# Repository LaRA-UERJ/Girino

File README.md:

# Girino
Plataforma didática do LaRA para ensino de controle de motores DC. Integra microcontrolador, driver MOSFET e encoder em uma bancada compacta para introdução prática à leitura de sensores, modulação PWM e controle em malha fechada.

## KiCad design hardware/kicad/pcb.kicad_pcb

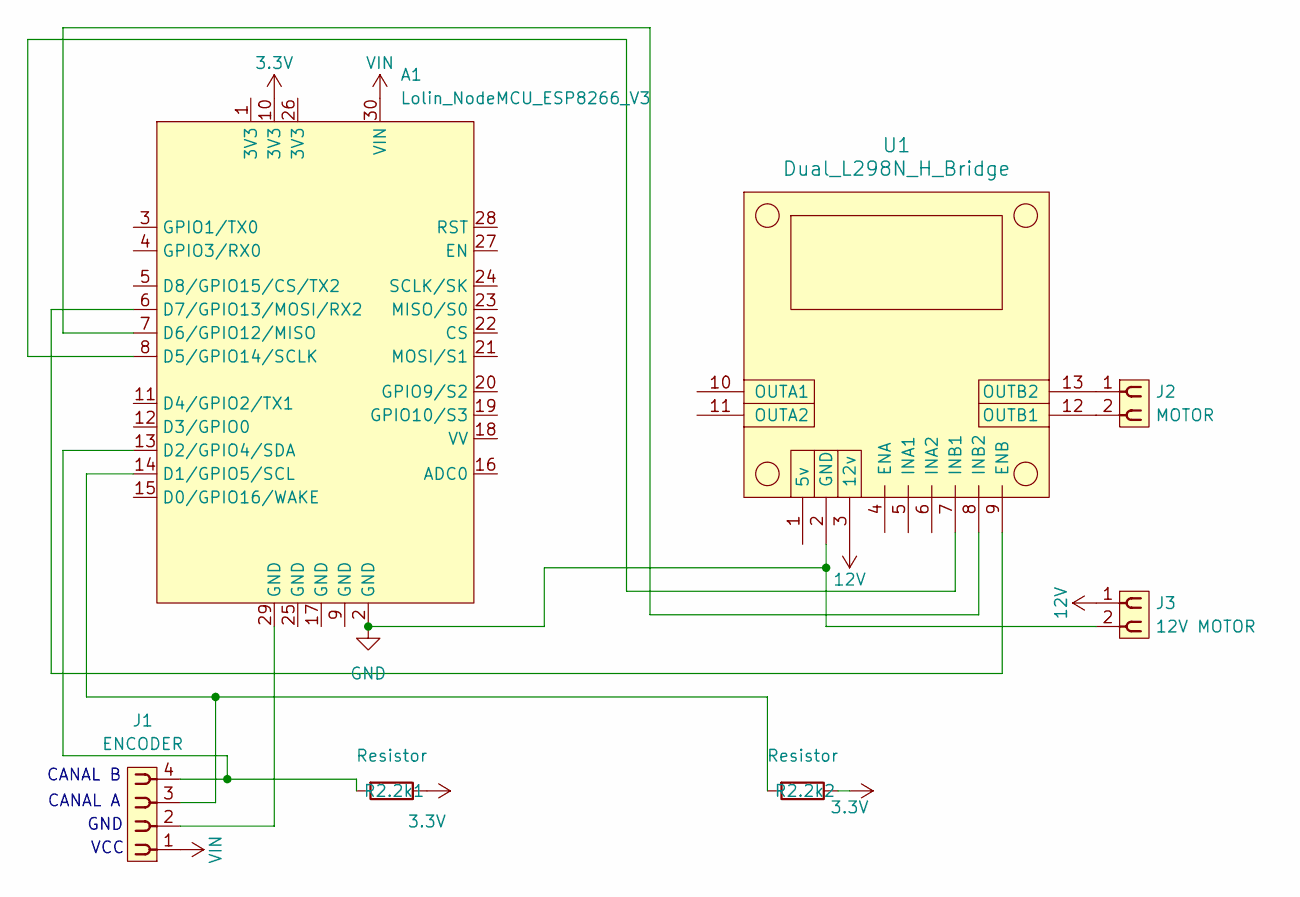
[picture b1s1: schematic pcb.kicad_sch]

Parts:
A1: Lolin_NodeMCU_ESP8266_V3; Lolin_NodeMCU_ESP8266
J1: ENCODER; PinSocket_1x04_P2.54mm_Vertical
J2: MOTOR; PinSocket_1x02_P2.54mm_Vertical
J3: 12V MOTOR; PinSocket_1x02_P2.54mm_Vertical
R2.2k1, R2.2k2: Resistor; R_Axial_DIN0207_L6.3mm_D2.5mm_P10.16mm_Horizontal
U1: Dual_L298N_H_Bridge

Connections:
3.3V: A1.10 (3V3), R2.2k1.2, R2.2k2.2
12V: J3.1, U1.3 (12v)
GND: A1.2 (GND), J3.2, U1.2 (GND)
unnamed: A1.14 (D1/GPIO5/SCL), J1.3, R2.2k2.1
unnamed: A1.13 (D2/GPIO4/SDA), J1.4, R2.2k1.1
unnamed: A1.8 (D5/GPIO14/SCLK), U1.7 (INB1)
unnamed: A1.7 (D6/GPIO12/MISO), U1.8 (INB2)
unnamed: A1.6 (D7/GPIO13/MOSI/RX2), U1.9 (ENB)
unnamed: A1.29 (GND), J1.2
unnamed: J2.2, U1.12 (OUTB1)
unnamed: J2.1, U1.13 (OUTB2)
VIN: A1.30 (VIN), J1.1

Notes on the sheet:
VCC
GND
CANAL B
CANAL A

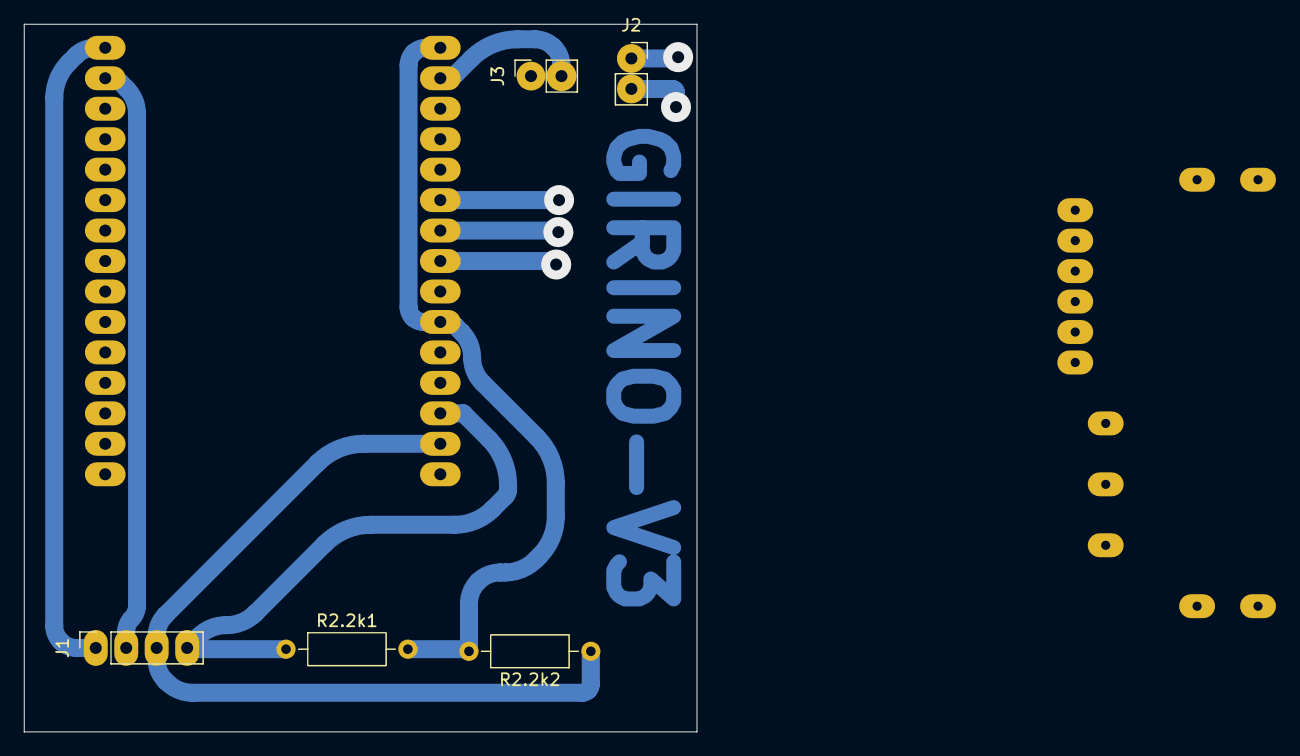
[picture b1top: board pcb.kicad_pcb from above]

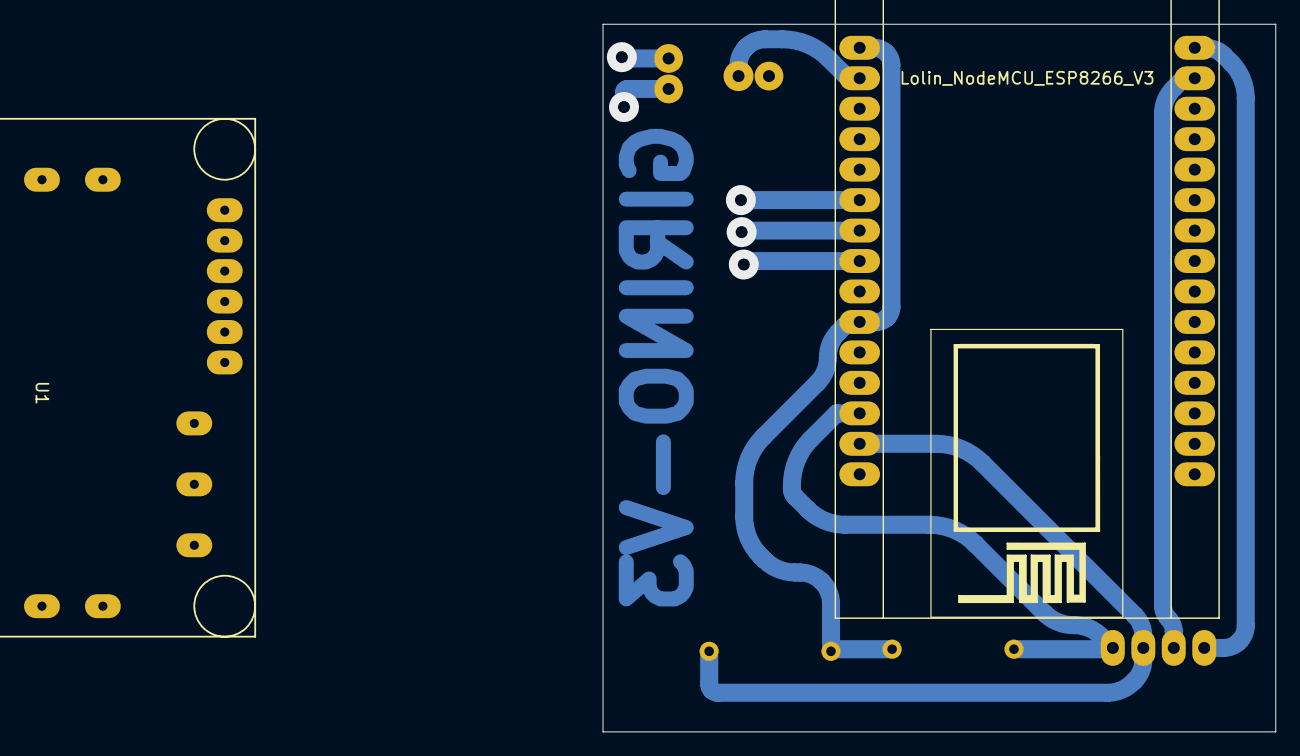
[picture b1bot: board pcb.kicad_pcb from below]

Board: 2 copper layers, 56.1 x 59.0 mm, 7 parts (2 on the bottom side), 12 nets.

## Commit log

2026-05-27 docs: adicionar AGENTS.md com contexto para agentes de IA
2026-05-27 docs: adicionar levantamento bibliográfico com ~55 referências para artigo
    - docs/referencias-pesquisa.md: referências organizadas por relevância
    - Tier 1: trabalhos diretamente relacionados (motor DC + encoder + PID + educação)
    - Plataformas open-source: MotoShield, AutomationShield, OpenMCT, TCLab
    - Publicações brasileiras: CBA, SBAI, COBENGE
    - ESP8266/ESP32 para ensino de controle
    - Simulação vs hardware real
2026-05-27 docs: adicionar análise comparativa e referências RBEF
    - docs/analise-comparativa.md: review de 7 trabalhos relacionados (Cabral
    2025, Alexandre 2025, Segundo 2019, MotoShield, OpenMCT, Reck 2015,
    TCLab), tabela comparativa geral, gap analysis, argumentação para artigo,
    estratégia de publicação
    - docs/referencias-pesquisa.md: +15 referências (13 papers RBEF + 2 revisões
    sistemáticas brasileiras), seção de veículos recomendados
